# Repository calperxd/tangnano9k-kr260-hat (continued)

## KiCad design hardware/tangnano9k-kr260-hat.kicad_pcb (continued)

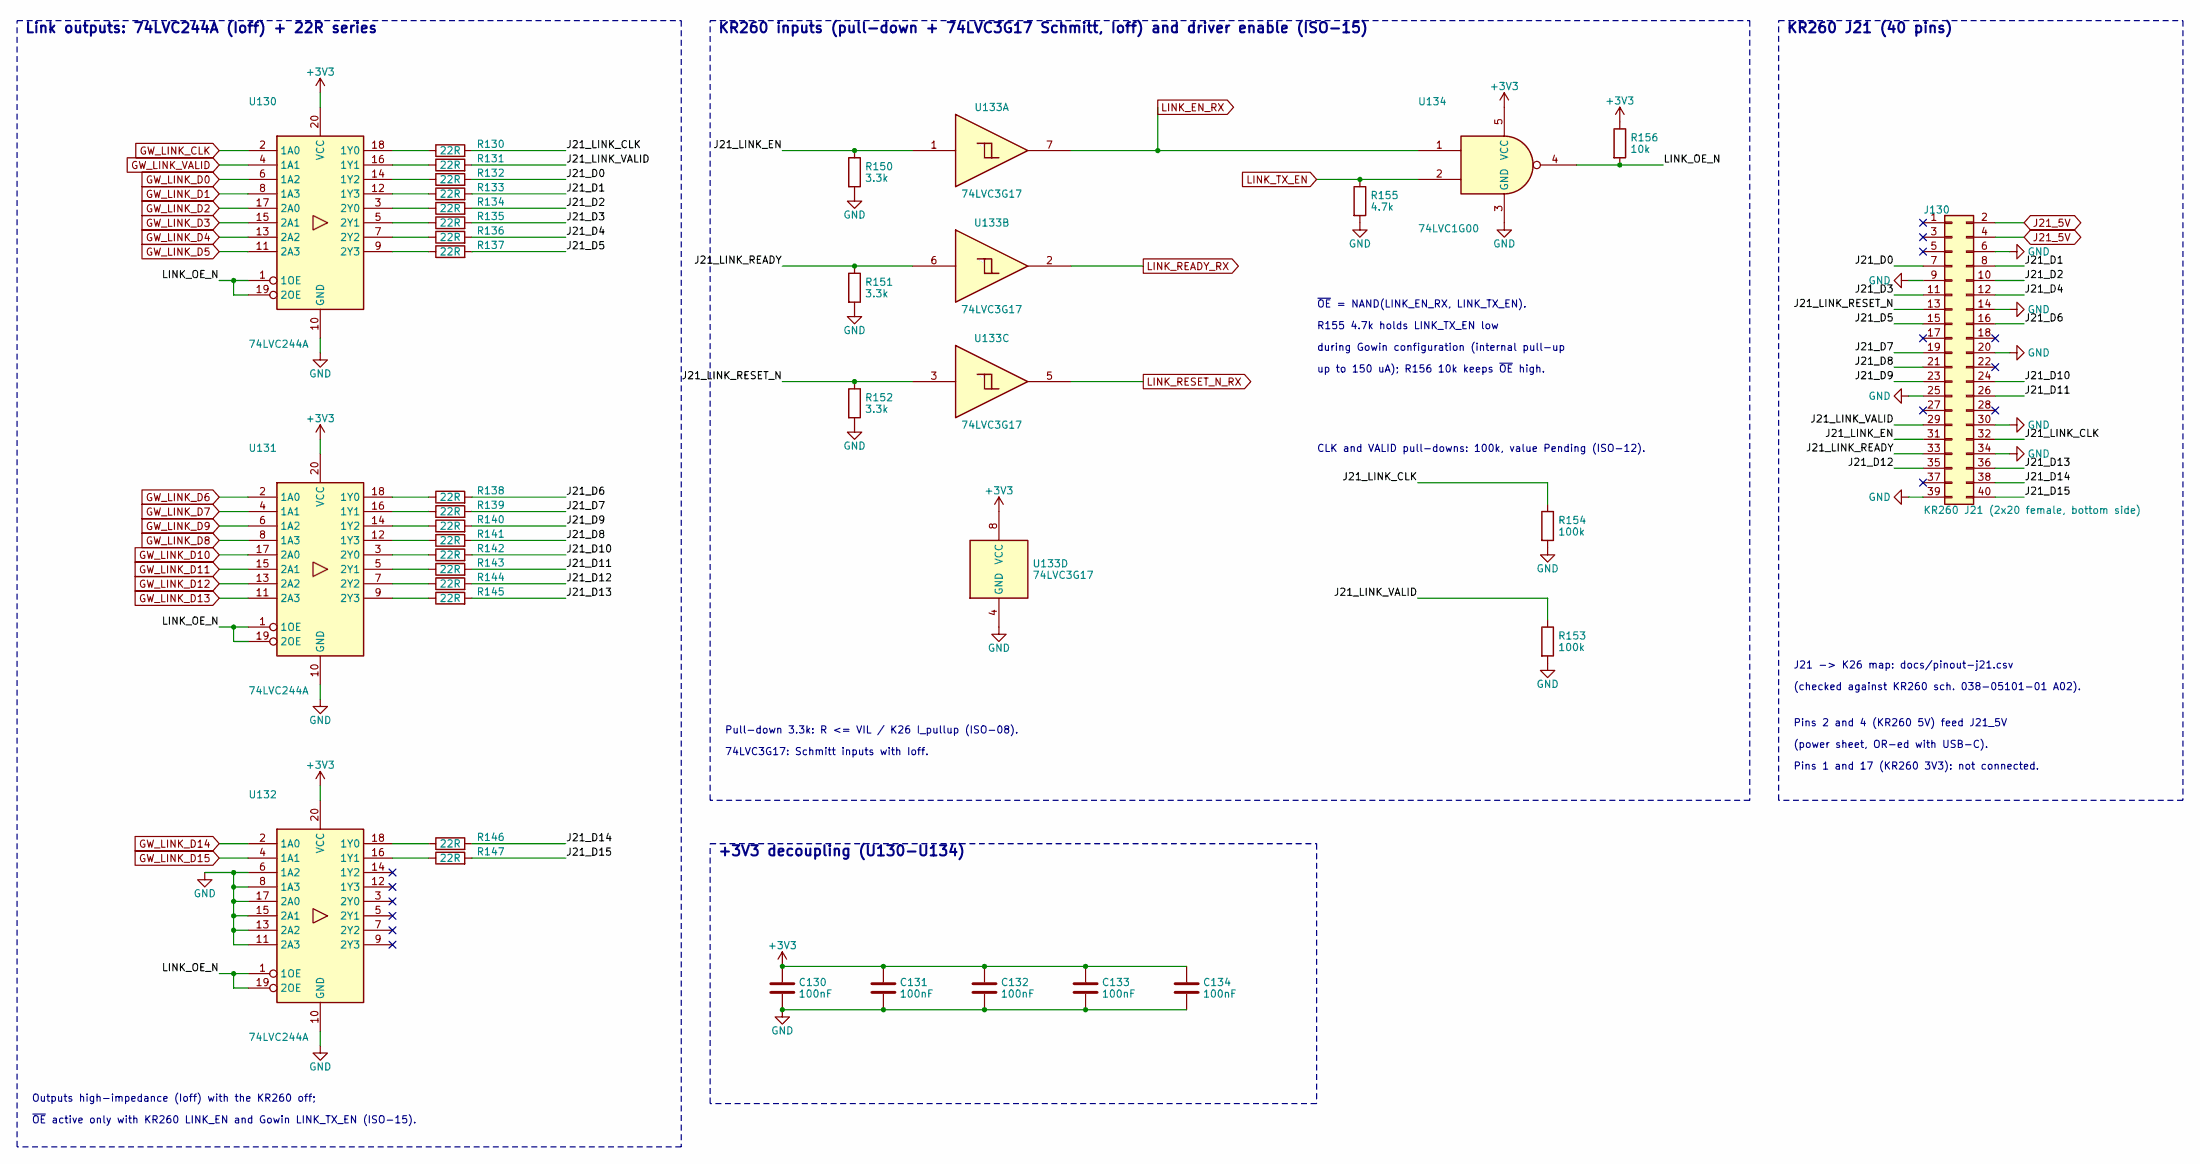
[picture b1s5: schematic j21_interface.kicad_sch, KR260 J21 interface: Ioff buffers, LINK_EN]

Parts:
C130, C131, C132, C133, C134: 100nF; C_0402_1005Metric
J130: KR260 J21 (2x20 female, bottom side); PinSocket_2x20_P2.54mm_Vertical
R130, R131, R132, R133, R134, R135, R136, R137, R138, R139, R140, R141, R142, R143, R144, R145, R146, R147: 22R; R_0402_1005Metric
R150, R151, R152: 3.3k; R_0402_1005Metric
R153, R154: 100k; R_0402_1005Metric
R155: 4.7k; R_0402_1005Metric
R156: 10k; R_0402_1005Metric
U130, U131, U132: 74LVC244A; TSSOP-20_4.4x6.5mm_P0.65mm
U133: 74LVC3G17; VSSOP-8_2.3x2mm_P0.5mm
U134: 74LVC1G00; SOT-23-5

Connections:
+3V3: C130.1, C131.1, C132.1, C133.1, C134.1, R156.1, U130.20 (VCC), U131.20 (VCC), U132.20 (VCC), U133.8 (VCC), U134.5 (VCC); also elsewhere on the board
/j21_interface/J21_D0: J130.7, R132.2
/j21_interface/J21_D1: J130.8, R133.2
/j21_interface/J21_D2: J130.10, R134.2
/j21_interface/J21_D3: J130.11, R135.2
/j21_interface/J21_D4: J130.12, R136.2
/j21_interface/J21_D5: J130.15, R137.2
/j21_interface/J21_D6: J130.16, R138.2
/j21_interface/J21_D7: J130.19, R139.2
/j21_interface/J21_D8: J130.21, R141.2
/j21_interface/J21_D9: J130.23, R140.2
/j21_interface/J21_D10: J130.24, R142.2
/j21_interface/J21_D11: J130.26, R143.2
/j21_interface/J21_D12: J130.35, R144.2
/j21_interface/J21_D13: J130.36, R145.2
/j21_interface/J21_D14: J130.38, R146.2
/j21_interface/J21_D15: J130.40, R147.2
/j21_interface/J21_LINK_CLK: J130.32, R130.2, R154.1
/j21_interface/J21_LINK_EN: J130.31, R150.1, U133.1
/j21_interface/J21_LINK_READY: J130.33, R151.1, U133.6
/j21_interface/J21_LINK_RESET_N: J130.13, R152.1, U133.3
/j21_interface/J21_LINK_VALID: J130.29, R131.2, R153.1
/j21_interface/LINK_OE_N: R156.2, U130.1 (1OE), U130.19 (2OE), U131.1 (1OE), U131.19 (2OE), U132.1 (1OE), U132.19 (2OE), U134.4
GND: C130.2, C131.2, C132.2, C133.2, C134.2, J130.6, J130.9, J130.14, J130.20, J130.25, J130.30, J130.34, J130.39, R150.2, R151.2, R152.2, R153.2, R154.2, R155.2, U130.10 (GND), U131.10 (GND), U132.6 (1A2), U132.8 (1A3), U132.10 (GND), U132.11 (2A3), U132.13 (2A2), U132.15 (2A1), U132.17 (2A0), U133.4 (GND), U134.3 (GND); also elsewhere on the board
GW_LINK_CLK: U130.2 (1A0); also elsewhere on the board
GW_LINK_D0: U130.6 (1A2); also elsewhere on the board
GW_LINK_D1: U130.8 (1A3); also elsewhere on the board
GW_LINK_D2: U130.17 (2A0); also elsewhere on the board
GW_LINK_D3: U130.15 (2A1); also elsewhere on the board
GW_LINK_D4: U130.13 (2A2); also elsewhere on the board
GW_LINK_D5: U130.11 (2A3); also elsewhere on the board
GW_LINK_D6: U131.2 (1A0); also elsewhere on the board
GW_LINK_D7: U131.4 (1A1); also elsewhere on the board
GW_LINK_D8: U131.8 (1A3); also elsewhere on the board
GW_LINK_D9: U131.6 (1A2); also elsewhere on the board
GW_LINK_D10: U131.17 (2A0); also elsewhere on the board
GW_LINK_D11: U131.15 (2A1); also elsewhere on the board
GW_LINK_D12: U131.13 (2A2); also elsewhere on the board
GW_LINK_D13: U131.11 (2A3); also elsewhere on the board
GW_LINK_D14: U132.2 (1A0); also elsewhere on the board
GW_LINK_D15: U132.4 (1A1); also elsewhere on the board
GW_LINK_VALID: U130.4 (1A1); also elsewhere on the board
J21_5V: J130.2, J130.4; also elsewhere on the board
LINK_EN_RX: U133.7, U134.1; also elsewhere on the board
LINK_READY_RX: U133.2; also elsewhere on the board
LINK_RESET_N_RX: U133.5; also elsewhere on the board
LINK_TX_EN: R155.1, U134.2; also elsewhere on the board
unnamed: R130.1, U130.18 (1Y0)
unnamed: R131.1, U130.16 (1Y1)
unnamed: R132.1, U130.14 (1Y2)
unnamed: R133.1, U130.12 (1Y3)
unnamed: R134.1, U130.3 (2Y0)
unnamed: R135.1, U130.5 (2Y1)
unnamed: R136.1, U130.7 (2Y2)
unnamed: R137.1, U130.9 (2Y3)
unnamed: R138.1, U131.18 (1Y0)
unnamed: R139.1, U131.16 (1Y1)
unnamed: R140.1, U131.14 (1Y2)
unnamed: R141.1, U131.12 (1Y3)
unnamed: R142.1, U131.3 (2Y0)
unnamed: R143.1, U131.5 (2Y1)
unnamed: R144.1, U131.7 (2Y2)
unnamed: R145.1, U131.9 (2Y3)
unnamed: R146.1, U132.18 (1Y0)
unnamed: R147.1, U132.16 (1Y1)

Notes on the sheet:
Link outputs: 74LVC244A (Ioff) + 22R series
Outputs high-impedance (Ioff) with the KR260 off;
~{OE} active only with KR260 LINK_EN and Gowin LINK_TX_EN (ISO-15).
KR260 inputs (pull-down + 74LVC3G17 Schmitt, Ioff) and driver enable (ISO-15)
Pull-down 3.3k: R <= VIL / K26 I_pullup (ISO-08).
74LVC3G17: Schmitt inputs with Ioff.
~{OE} = NAND(LINK_EN_RX, LINK_TX_EN).
R155 4.7k holds LINK_TX_EN low
during Gowin configuration (internal pull-up
up to 150 uA); R156 10k keeps ~{OE} high.
CLK and VALID pull-downs: 100k, value Pending (ISO-12).
+3V3 decoupling (U130-U134)
KR260 J21 (40 pins)
J21 -> K26 map: docs/pinout-j21.csv
(checked against KR260 sch. 038-05101-01 A02).
Pins 2 and 4 (KR260 5V) feed J21_5V
(power sheet, OR-ed with USB-C).
Pins 1 and 17 (KR260 3V3): not connected.

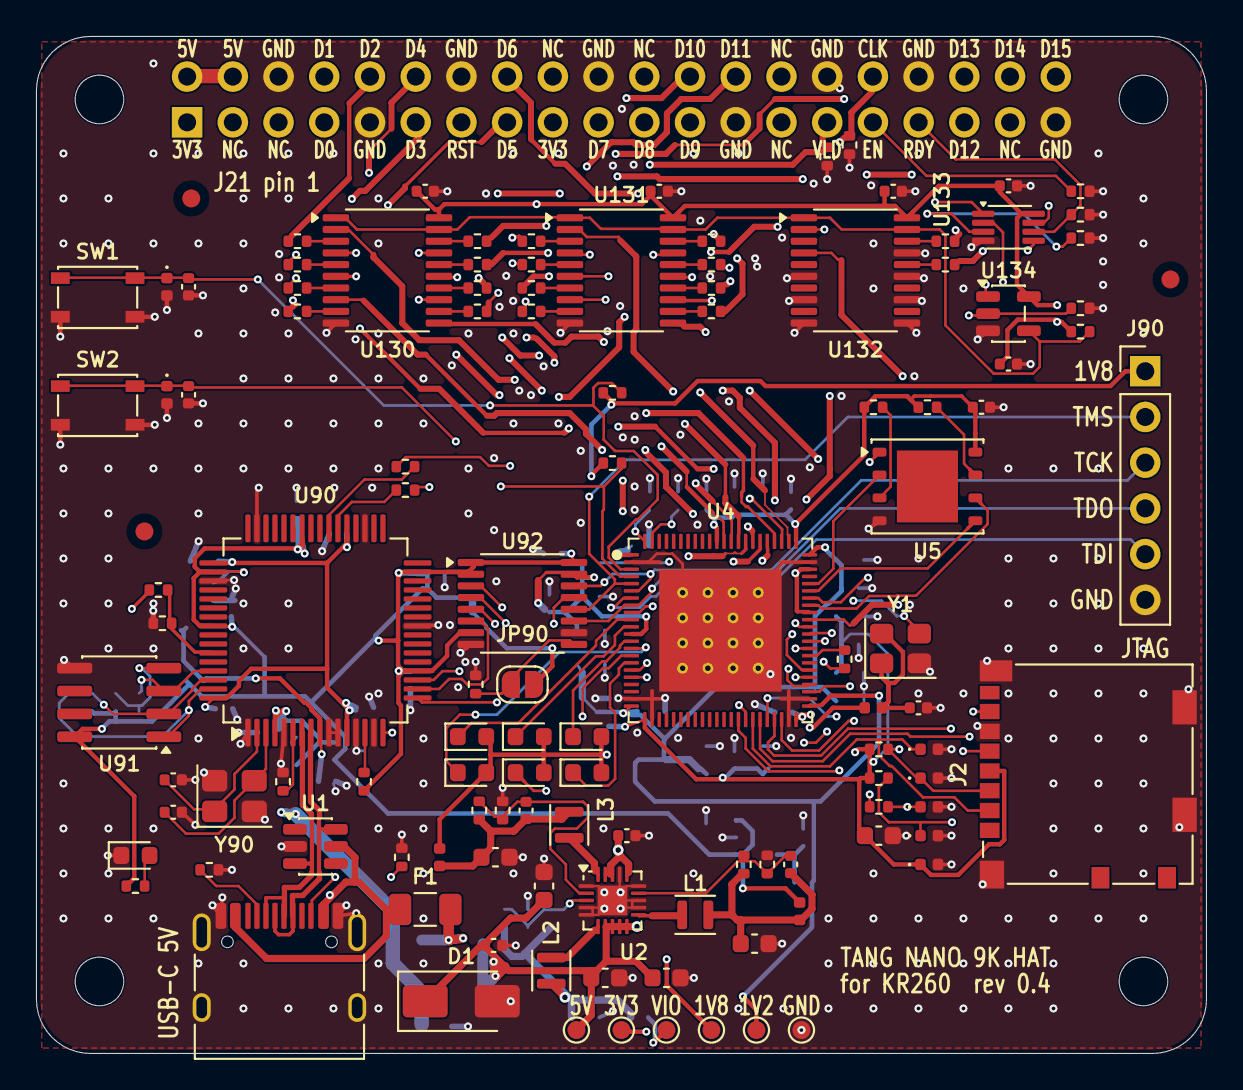
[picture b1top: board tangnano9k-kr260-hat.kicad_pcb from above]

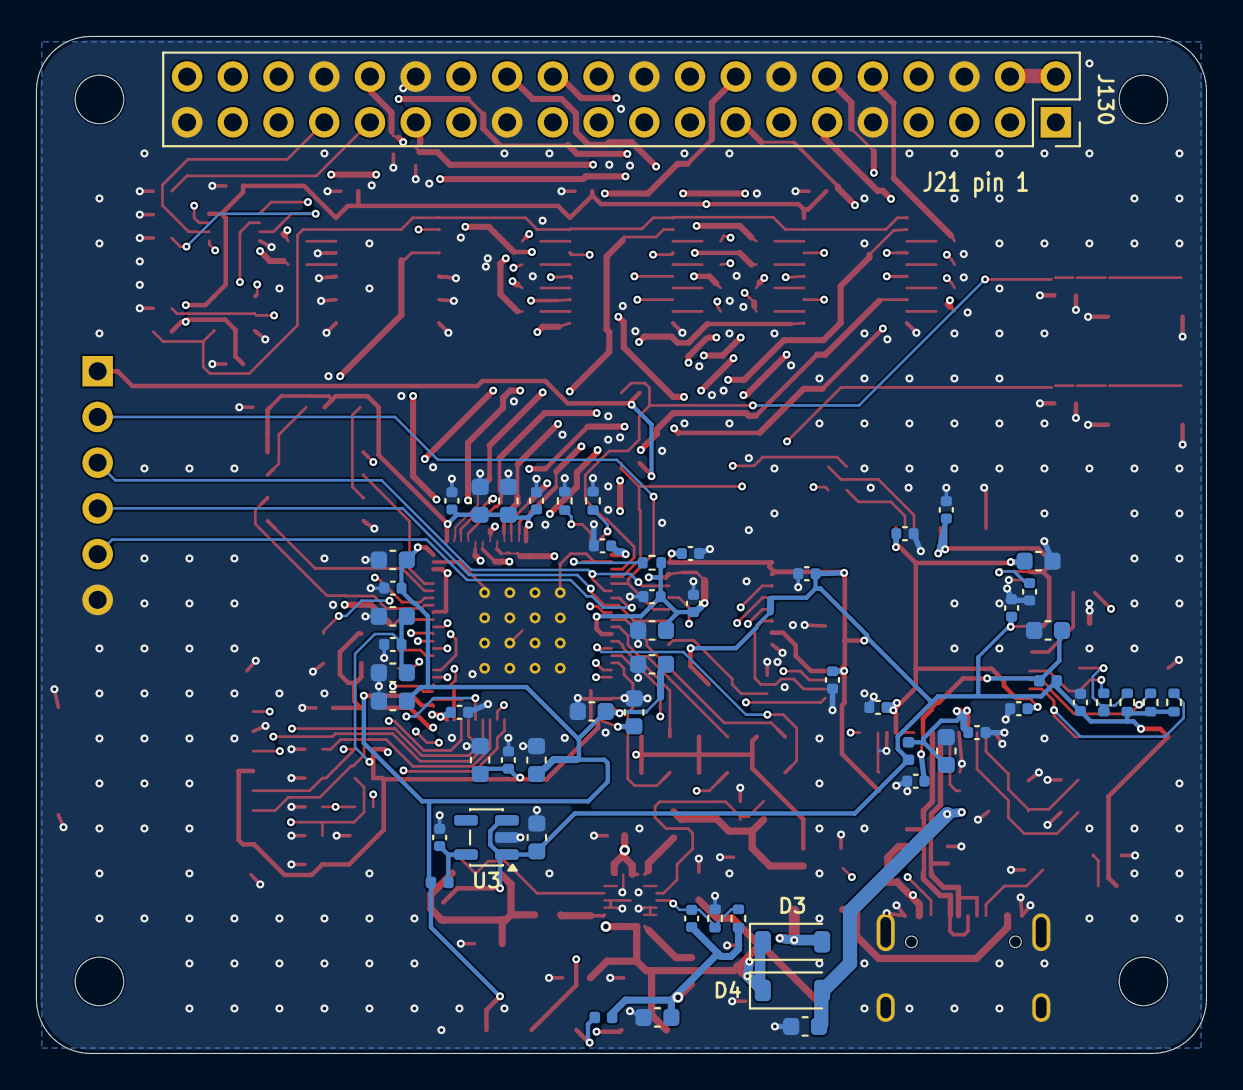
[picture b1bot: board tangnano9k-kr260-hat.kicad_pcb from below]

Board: 4 copper layers, 65.0 x 56.5 mm, 181 parts (58 on the bottom side), 136 nets.

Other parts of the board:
FID1, FID2, FID3: Fiducial_1mm_Mask2mm
H1, H2, H3, H4: MountingHole_2.7mm_M2.5

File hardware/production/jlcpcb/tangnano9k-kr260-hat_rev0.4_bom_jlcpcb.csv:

Comment,Designator,Footprint,LCSC Part #
18pF,"C1,C2,C3",C_0402_1005Metric,C1549
10uF,"C4,C5,C11,C14,C30,C32,C33,C34,C35,C36,C39,C40,C41,C42,C43,C44,C71",C_0603_1608Metric,C19702
22uF,"C6,C7,C8,C9",C_0603_1608Metric,C86295
2.2uF,"C10,C12,C13",C_0402_1005Metric,C386077
100nF,"C31,C37,C38,C45,C46,C47,C48,C49,C50,C51,C52,C70,C91,C93,C94,C96,C97,C98,C99,C100,C101,C102,C105,C106,C107,C130,C131,C132,C133,C134",C_0402_1005Metric,C1525
4.7uF,"C90,C92",C_0603_1608Metric,C19666
3.3uF,C95,C_0603_1608Metric,C51412
27pF,"C103,C104",C_0402_1005Metric,C1557
SMAJ5.0A,D1,D_SMA,C83329
LTST-C190KFKT,D2,LED_0603_1608Metric,C157740
B5819W SL,"D3,D4",D_SOD-123,C8598
0402ESDA-05N,"D30,D31,D70,D71,D72,D73,D74",D_0402_1005Metric,C316049
LTST-C190KFKT,"D32,D33,D34,D35,D36,D37",LED_0603_1608Metric,C157740
nSMD050-33V,F1,Fuse_1206_3216Metric,C70077
UPZ1005D121-1R3TF,"FB1,FB2,FB3,FB4,FB30,FB90,FB91",L_0402_1005Metric,C96993
TYPE-C-31-M-12,J1,USB_C_Receptacle_HRO_TYPE-C-31-M-12,C165948
1040310811,J2,microSD_HC_Molex_104031-0811,C585350
PZ254V-11-06P,J90,PinHeader_1x06_P2.54mm_Vertical,C492405
DS1023-2*20SF11,J130,PinSocket_2x20_P2.54mm_Vertical,C132132
DFE201610P-2R2M=P2,"L1,L2,L3",L_Murata_DFE201610P,C237554
5.1k,"R1,R2",R_0402_1005Metric,C25905
680k,"R3,R5",R_0402_1005Metric,C163456
150k,"R4,R6,R8",R_0402_1005Metric,C25755
300k,R7,R_0402_1005Metric,C25774
1k,"R9,R91",R_0402_1005Metric,C11702
4.7k,"R10,R30,R31,R32,R70,R71,R155",R_0402_1005Metric,C25900
10k,"R11,R33,R34,R72,R73,R92,R93,R94,R96,R156",R_0402_1005Metric,C25744
22R,"R35,R97,R98,R130,R131,R132,R133,R134,R135,R136,R137,R138,R139,R140,R141,R142,R143,R144,R145,R146,R147",R_0402_1005Metric,C25092
0R,R74,R_0402_1005Metric,C17168
12k 1%,R90,R_0402_1005Metric,C25752
2.2k,R95,R_0402_1005Metric,C25879
3.3k,"R150,R151,R152",R_0402_1005Metric,C25890
100k,"R153,R154",R_0402_1005Metric,C25741
PTS810SJG250SMTRLFS,SW1,SW_SPST_PTS810,C221895
PTS810SJG250SMTRLFS,SW2,SW_SPST_PTS810,C221895
USBLC6-2SC6,U1,SOT-23-6,C7519
TMI7003C,U2,QFN-20-1EP_3x3mm_P0.4mm_EP1.65x1.65mm,C840566
ME6211C12M5G-N,U3,SOT-23-5,C236672
GW1NR-LV9QN88PC6/I5,U4,GW1NR_QN88P_10x10mm_P0.4mm_EP6.8mm,
W25Q32JVZPIQ,U5,WSON-8-1EP_6x5mm_P1.27mm_EP3.4x4mm,C571260
FT2232HL-REEL,U90,LQFP-64_10x10mm_P0.5mm,C27882
93LC56BT-I/SN,U91,SOIC-8_3.9x4.9mm_P1.27mm,C6164
SN74AVC4T774PWR,U92,TSSOP-16_4.4x5mm_P0.65mm,C129363
SN74LVC244APWR,"U130,U131,U132",TSSOP-20_4.4x6.5mm_P0.65mm,C7668
SN74LVC3G17DCUR,U133,VSSOP-8_2.3x2mm_P0.5mm,C68245
SN74LVC1G00DBVR,U134,SOT-23-5,C7826
OT2JI-111-27M,Y1,Oscillator_SMD_Abracon_ASE-4Pin_3.2x2.5mm,C20617591
X322512MSB4SI,Y90,Crystal_SMD_3225-4Pin_3.2x2.5mm,C9002
